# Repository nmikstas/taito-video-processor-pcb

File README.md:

# taito-video-processor-pcb
Reproduction of the Taito video processor PCB. The PCB is designed with Kicad. This project is now complete and verified working!

# Folder Structure
* BOM - Bill of materials
* Gerbers -Gerber files
* pcb - Kicad design files

# PCB Specifications
* Layers: 2
* Dimensions: 305mm X 280mm
* Different PCB Design: 1
* PCB Thickness: 1.6mm
* Surface Finish: HASL
* Castellated Holes: No
* Copper Weight: 1oz.

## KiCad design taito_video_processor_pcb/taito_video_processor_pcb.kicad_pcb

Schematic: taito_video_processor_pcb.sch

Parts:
BT1: 3.6V; battery
BT2: Battery_Cell; CR2032
C1, C2, C3, C4, C5, C6, C7, C8, C10, C11, C12, C13, C15, C16, C17, C18, C19, C20, C21, C23, C24, C25, C26, C27, C28, C29, C30, C32, C33, C34, C35, C36, C37, C38, C39, C40, C41, C43, C46, C47, C48, C49, C50, C51, C52, C53, C54, C55, C56, C57, C58, C59, C60, C62, C64, C66, C67, C68, C69, C70, C71, C72, C73, C74, C75, C76, C78, C79, C81, C82, C83, C84, C85, C86, C87, C91, C92, C93, C94, C95, C99, C100, C102, C103, C104, C105, C106, C107, C108, C999: .1uf; GenericComp
C9, C22, C42, C44, C45, C61, C63, C77, C80: 10uf; CapA
C14, C31: 100pf; GenericComp
C65, C96, C97, C98, C110, C111, C112, C113: 470pf; GenericComp
C88, C89, C90, C109: 100uf; CapB
C101: 10uf; GenericComp
D1: FR156; GenericComp
FB1, FB2, FB3, FB4, FB5, FB6, FB7, FB8, FB9, FB10, FB11, FB12, FB13, FB14: Ferrite_Bead; FB
J1, J2: 14pin; con_14pin
J3, J6: 50pin; 50Pin
J19: 2pin; con_2pin
JB2: W1; JMP
LED1, LED2, LED3, LED4, LED5, LED6: LED
Q1, Q2, Q3, Q4, Q5, Q6, Q7: 2N3904; Trans
Q8: 2N3905; Trans
R1, R9, R10, R11, R12, R21, R22, R23, R24, R25, R26, R27, R36, R51, R52, R53, R54, R55, R56, R57, R58: 33; GenericComp
R2: 1.5k; GenericComp
R3, R4, R5, R15, R18, R49: 270; GenericComp
R6, R38, R60, R62, R66, R67, R68, R69: 3.3k; GenericComp
R7: 220; GenericComp
R8: 2.2k; GenericComp
R13, R20, R46: 82; GenericComp
R14, R19, R28, R48: 180; GenericComp
R16, R17, R45, R65: 150; GenericComp
R29, R30, R31, R32, R33, R47: 470; GenericComp
R34: 680; GenericComp
R35, R61: 390; GenericComp
R37, R50, R59: 47k; GenericComp
R39, R40, R41, R42, R43, R44: 330; GenericComp
R63: 1k; GenericComp
R64: 120; GenericComp
RP1: 1K; RP
RP2: 47K; RP
RP3, RP4, RP5: 3.3k; RP
SW1: SW_Push; Switch
SW2: Switch; Pushbutton
TP1, TP3, TP4: TestPoint; TPA
TP2: 10MHz; TPA
TP5, TP6, TP7, TP8: TestPoint; TPB
U1, U2, U69, U75: 245_1; DIP20
U3, U4: 2114; DIP18
U5, U6, U21, U55, U73, U74, U81, U104: 157_1; DIP16
U7, U36, U89: LS74; DIP14
U8, U9, U22, U49, U67, U88: LS32; DIP14
U10, U11, U12, U13, U14, U15, U16, U17, U26, U27, U28, U29, U30, U31, U32, U33, U41, U42, U43, U44, U45, U46, U47, U48, U59, U60, U61, U62, U63, U64, U65, U66: 4116; DIP16
U18: 68A45; DDIP40
U19: 86_2; DIP14
U20: 86_1; DIP14
U23: 161_1; DIP16
U24, U39, U90: LS04; DIP14
U25, U70, U71, U91, U92, U93, U94: 374_1; DIP20
U34, U72: LS374; DIP20
U35, U52, U53, U54: 153_1; DIP16
U37, U101: LS08; DIP14
U38: 74S113; DIP14
U40, U58: 7417; DIP14
U50: 86_3; DIP14
U51: LS86; DIP14
U56: 2148_1; DIP18
U57: 2148_2; DIP18
U68, U83, U84: 244_2; DIP20
U76: 273_1; DIP20
U77, U78, U79, U80: 373; DIP20
U82: 68A09E; DDIP40
U85, U86: 6514_1; DIP18
U87: LS139; DIP16
U95, U96, U105, U106, U107, U108, U109, U110: 299_1; DIP20
U97, U98: 244_1; DIP20
U99: 138_1; DIP16
U100, U103: LS00; DIP14
U102: LS10; DIP14
Y1: Crystal

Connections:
+5V: C1.1, C10.1, C11.1, C12.1, C13.1, C15.1, C17.1, C20.1, C23.1, C26.1, C27.1, C28.1, C29.1, C30.1, C32.1, C35.1, C39.1, C45.1, C50.1, C51.1, C52.1, C56.1, C60.1, C64.1, C66.1, C67.1, C68.1, C69.1, C70.1, C71.1, C75.1, C79.1, C81.1, C82.1, C83.1, C84.1, C85.1, C86.1, C90.1, C91.1, C92.1, C93.1, C94.1, C95.1, C99.1, C100.1, C102.1, C103.1, C104.1, C105.1, C106.1, C107.1, C108.1, C999.1, FB8.2, LED1.2 (A), LED2.2 (A), LED3.2 (A), LED4.2 (A), LED5.2 (A), LED6.2 (A), Q1.3 (C), Q8.1 (E), R3.1, R4.1, R5.1, R6.1, R28.2, R38.1, R50.1, R59.2, R60.1, R62.1, R63.2, R66.1, R67.1, R68.1, R69.1, RP1.1, RP3.1, RP4.1, RP5.1, U1.20 (VCC), U2.20 (VCC), U3.18 (VSS), U4.18 (VSS), U5.16 (VCC), U6.16 (VCC), U7.14 (VCC), U8.14 (VCC), U9.14 (VCC), U10.9, U11.9, U12.9, U13.9, U14.9, U15.9, U16.9, U17.9, U18.3 (LPSTB), U18.20 (PWR), U19.14 (VCC), U20.14 (VCC), U21.16 (VCC), U22.14 (VCC), U23.16 (VCC), U24.14 (VCC), U25.20 (VCC), U26.9, U27.9, U28.9, U29.9, U30.9, U31.9, U32.9, U33.9, U34.20 (VCC), U35.16 (VCC), U36.14 (VCC), U37.14 (VCC), U38.14 (VCC), U39.14 (VCC), U40.14 (VCC), U41.9, U42.9, U43.9, U44.9, U45.9, U46.9, U47.9, U48.9, U49.14 (VCC), U50.14 (VCC), U51.14 (VCC), U52.16 (VCC), U53.16 (VCC), U54.16 (VCC), U55.16 (VCC), U56.18 (VCC), U57.18 (VCC), U58.14 (VCC), U59.9, U60.9, U61.9, U62.9, U63.9, U64.9, U65.9, U66.9, U67.14 (VCC), U68.20 (VCC), U69.20 (VCC), U70.20 (VCC), U71.20 (VCC), U72.20 (VCC), U73.16 (VCC), U74.16 (VCC), U75.20 (VCC), U76.20 (VCC), U77.20 (VCC), U78.20 (VCC), U79.20 (VCC), U80.20 (VCC), U81.16 (VCC), U82.7 (VCC), U83.20 (VCC), U84.20 (VCC), U87.16 (VCC), U88.14 (VCC), U89.14 (VCC), U90.14 (VCC), U91.20 (VCC), U92.20 (VCC), U93.20 (VCC), U94.20 (VCC), U95.20 (VCC), U96.20 (VCC), U97.20 (VCC), U98.20 (VCC), U99.16 (VCC), U101.14 (VCC), U102.14 (VCC), U103.14 (VCC), U104.16 (VCC), U105.20 (VCC), U106.20 (VCC), U107.20 (VCC), U108.20 (VCC), U109.20 (VCC), U110.20 (VCC)
+12V: C16.1, C18.1, C19.1, C21.1, C22.1, C36.1, C37.1, C41.1, C42.1, C55.1, C59.1, C61.1, C72.1, C76.1, C77.1, C87.1, C89.1, FB10.2, U10.8, U11.8, U12.8, U13.8, U14.8, U15.8, U16.8, U17.8, U26.8, U27.8, U28.8, U29.8, U30.8, U31.8, U32.8, U33.8, U41.8, U42.8, U43.8, U44.8, U45.8, U46.8, U47.8, U48.8, U59.8, U60.8, U61.8, U62.8, U63.8, U64.8, U65.8, U66.8
-5V: C2.1, C3.1, C4.1, C5.1, C6.1, C7.1, C8.1, C9.2, C33.1, C34.1, C38.1, C40.1, C43.1, C44.2, C53.1, C54.1, C57.1, C58.1, C62.1, C63.2, C73.1, C74.1, C78.1, C80.2, C88.2, FB9.2, U10.1, U11.1, U12.1, U13.1, U14.1, U15.1, U16.1, U17.1, U26.1, U27.1, U28.1, U29.1, U30.1, U31.1, U32.1, U33.1, U41.1, U42.1, U43.1, U44.1, U45.1, U46.1, U47.1, U48.1, U59.1, U60.1, U61.1, U62.1, U63.1, U64.1, U65.1, U66.1
AEN: U70.1 (~OE), U71.1 (~OE), U88.6, U90.9, U101.13
BD0: R58.1, U17.2, U33.2, U48.2, U66.2
BD1: R57.1, U16.2, U32.2, U47.2, U65.2
BD2: R56.1, U15.2, U31.2, U46.2, U64.2
BD3: R55.1, U14.2, U30.2, U45.2, U63.2
BD4: R54.1, U13.2, U29.2, U44.2, U62.2
BD5: R53.1, U12.2, U28.2, U43.2, U61.2
BD6: R52.1, U11.2, U27.2, U42.2, U60.2
BD7: R51.1, U10.2, U26.2, U41.2, U59.2
BPWR: C101.1, Q8.3 (C), R61.1, R64.2, U85.18 (VCC), U86.18 (VCC), U100.14 (VCC)
CCLK: U18.21 (CCLK), U23.11 (Q3), U39.3, U102.3
CR0: U74.6, U104.12
CR1: U74.3, U104.9
CR2: U73.13, U104.7
CR3: U73.10, U104.4
CR4: U73.6, U81.12
CR5: U73.3, U81.9
CR6: U55.13, U81.7
CR7: U55.10, U81.4
CR8: U55.6, U72.19 (O7)
CR9: U55.3, U72.16 (O6)
D0: RP2.5, U69.11, U82.31 (D0)
D2: RP2.6, U69.13, U82.29 (D2)
D3: RP2.7, U69.14, U82.28 (D3)
D5: RP2.8, U69.16, U82.26 (D5)
D6: RP2.9, U69.17, U82.25 (D6)
D7: RP2.10, U69.18, U82.24 (D7)
DA0: J6.35, U8.1, U21.6, U39.13
DA1: J6.38, U21.3
DA2: J6.50, U6.13
DA3: J6.49, U6.10
DA4: J6.48, U6.6
DA5: J6.47, U6.3
DA6: J6.36, U5.13
DA7: J6.45, U5.10
DA8: J6.37, U5.6
DA9: J6.40, U5.3
DD0: J6.1, U2.11
DD1: J6.4, U2.12
DD2: J6.3, U2.13
DD3: J6.6, U2.14
DD4: J6.5, U2.15
DD5: J6.8, U2.16
DD6: J6.7, U2.17
DD7: J6.9, U2.18
DPMUX: U2.19 (~E), U36.9 (2Q), U37.2, U37.5
DRW: J6.2, U2.1 (D), U21.13
E: U18.23 (E), U25.6, U37.4, U91.11 (C), U92.11 (C), U93.11 (C), U94.11 (C), U102.9, U103.12
GND: C1.2, C2.2, C3.2, C4.2, C5.2, C6.2, C7.2, C8.2, C9.1, C10.2, C11.2, C12.2, C13.2, C14.2, C15.2, C16.2, C17.2, C18.2, C19.2, C20.2, C21.2, C22.2, C23.2, C24.2, C25.2, C26.2, C27.2, C28.2, C29.2, C30.2, C31.2, C32.2, C33.2, C34.2, C35.2, C36.2, C37.2, C38.2, C39.2, C40.2, C41.2, C42.2, C43.2, C44.1, C45.2, C46.2, C47.2, C48.2, C49.2, C50.2, C51.2, C52.2, C53.2, C54.2, C55.2, C56.2, C57.2, C58.2, C59.2, C60.2, C61.2, C62.2, C63.1, C64.2, C65.2, C66.2, C67.2, C68.2, C69.2, C70.2, C71.2, C72.2, C73.2, C74.2, C75.2, C76.2, C77.2, C78.2, C79.2, C80.1, C81.2, C82.2, C83.2, C84.2, C85.2, C86.2, C87.2, C88.1, C89.2, C90.2, C91.2, C92.2, C93.2, C94.2, C95.2, C96.2, C97.2, C98.2, C99.2, C100.2, C101.2, C102.2, C103.2, C104.2, C105.2, C106.2, C107.2, C108.2, C109.1, C110.2, C111.2, C112.2, C113.2, C999.2, J1.3, J1.5, J1.7, J1.11, J2.4, J3.1, J3.2, J3.4, J6.10, J6.12, J6.24, J6.26, J6.28, J6.29, J6.44, J6.46, J19.1, JB2.2, R2.2, R16.1, R17.1, R37.2, R45.1, RP2.1, SW1.2, SW2.2, U1.10 (GND), U2.10 (GND), U3.9 (GND), U4.9 (GND), U5.8 (GND), U5.15 (~E), U6.8 (GND), U6.15 (~E), U7.2 (1D), U7.7 (GND), U7.12 (2D), U8.7 (GND), U9.7 (GND), U9.12, U9.13, U10.16, U11.16, U12.16, U13.16, U14.16, U15.16, U16.16, U17.16, U18.1 (GND), U19.7 (GND), U20.7 (GND), U21.8 (GND), U21.15 (~E), U22.7 (GND), U23.3, U23.4, U23.5, U23.6, U23.8 (GND), U24.7 (GND), U25.1 (~OE), U25.10 (GND), U26.16, U27.16, U28.16, U29.16, U30.16, U31.16, U32.16, U33.16, U34.10 (GND), U35.1, U35.8 (GND), U35.15, U36.7 (GND), U37.7 (GND), U38.7 (GND), U39.5, U39.7 (GND), U40.7 (GND), U41.16, U42.16, U43.16, U44.16, U45.16, U46.16, U47.16, U48.16, U49.7 (GND), U50.7 (GND), U51.7 (GND), U51.9, U52.1, U52.8 (GND), U52.15, U53.1, U53.8 (GND), U53.15, U54.1, U54.8 (GND), U54.15, U55.8 (GND), U55.15 (~E), U56.8 (~CE), U56.9 (GND), U57.8 (~CE), U57.9 (GND), U58.7 (GND), U59.16, U60.16, U61.16, U62.16, U63.16, U64.16, U65.16, U66.16, U67.7 (GND), U68.1 (~E1), U68.10 (GND), U68.19 (~E2), U69.10 (GND), U70.10 (GND), U71.10 (GND), U72.1 (OE), U72.10 (GND), U73.8 (GND), U73.15 (~E), U74.8 (GND), U74.10, U74.15 (~E), U75.10 (GND), U76.10 (GND), U77.10 (GND), U78.10 (GND), U79.10 (GND), U80.10 (GND), U81.8 (GND), U81.15 (~E), U82.1 (GND), U82.39 (TSC), U83.1 (~E1), U83.10 (GND), U83.19 (~E2), U84.10 (GND), U85.9 (GND), U86.9 (GND), U87.8 (GND), U88.7 (GND), U88.12, U88.13, U89.3 (1CLK), U89.7 (GND), U90.1, U90.3, U90.7 (GND), U90.13, U91.1 (~OE), U91.10 (GND), U92.1 (~OE), U92.10 (GND), U93.1 (~OE), U93.10 (GND), U94.1 (~OE), U94.10 (GND), U95.10 (GND), U96.10 (GND), U97.1 (~E1), U97.10 (GND), U97.19 (~E2), U98.10 (GND), U99.8 (GND), U100.1, U100.2, U100.4, U100.5, U100.7 (GND), U100.9, U100.10, U101.7 (GND), U101.9, U101.10, U102.7 (GND), U103.7 (GND), U104.8 (GND), U104.15 (~E), U105.10 (GND), U106.10 (GND), U107.10 (GND), U108.10 (GND), U109.10 (GND), U110.10 (GND)
HS: U18.39 (HS), U40.1
INV: J6.42, TP1.1, U24.13, U81.1 (S), U103.9, U104.1 (S)
LA0: U71.19, U84.9, U87.14 (2A)
LA1: U71.16, U84.12, U87.13 (2B)
LA2: U54.5, U71.15, U84.7
LA3: U53.11, U71.12, U84.14
LA4: U53.5, U71.9, U84.5
LA5: U35.11, U71.6, U84.16
LA6: U35.5, U71.5, U84.3
LA7: U52.11, U71.2, U84.18
LA8: U52.5, U70.19, U98.18
LA9: U54.6, U70.16, U98.3
LA10: U53.10, U70.15, U98.16
LA11: U53.6, U70.12, U98.5
LA12: U35.10, U70.9, U98.12
LA13: U35.6, U70.6, U98.9
LA14: U52.10, U70.5, U98.7
LA15: U36.5 (1Q), U52.6
LS: U89.11 (2CLK), U102.6, U103.5, U103.10
M0: R25.1, RP1.6, U10.5, U11.5, U12.5, U13.5, U14.5, U15.5, U16.5, U17.5, U26.5, U27.5, U28.5, U29.5, U30.5, U31.5, U32.5, U33.5, U41.5, U42.5, U43.5, U44.5, U45.5, U46.5, U47.5, U48.5, U59.5, U60.5, U61.5, U62.5, U63.5, U64.5, U65.5, U66.5
M1: R27.1, RP1.7, U10.6, U11.6, U12.6, U13.6, U14.6, U15.6, U16.6, U17.6, U26.6, U27.6, U28.6, U29.6, U30.6, U31.6, U32.6, U33.6, U41.6, U42.6, U43.6, U44.6, U45.6, U46.6, U47.6, U48.6, U59.6, U60.6, U61.6, U62.6, U63.6, U64.6, U65.6, U66.6
M2: R26.1, RP1.9, U10.7, U11.7, U12.7, U13.7, U14.7, U15.7, U16.7, U17.7, U26.7, U27.7, U28.7, U29.7, U30.7, U31.7, U32.7, U33.7, U41.7, U42.7, U43.7, U44.7, U45.7, U46.7, U47.7, U48.7, U59.7, U60.7, U61.7, U62.7, U63.7, U64.7, U65.7, U66.7
M3: R11.1, RP1.4, U10.12, U11.12, U12.12, U13.12, U14.12, U15.12, U16.12, U17.12, U26.12, U27.12, U28.12, U29.12, U30.12, U31.12, U32.12, U33.12, U41.12, U42.12, U43.12, U44.12, U45.12, U46.12, U47.12, U48.12, U59.12, U60.12, U61.12, U62.12, U63.12, U64.12, U65.12, U66.12
M4: R24.1, RP1.8, U10.11, U11.11, U12.11, U13.11, U14.11, U15.11, U16.11, U17.11, U26.11, U27.11, U28.11, U29.11, U30.11, U31.11, U32.11, U33.11, U41.11, U42.11, U43.11, U44.11, U45.11, U46.11, U47.11, U48.11, U59.11, U60.11, U61.11, U62.11, U63.11, U64.11, U65.11, U66.11
M5: R23.1, RP1.10, U10.10, U11.10, U12.10, U13.10, U14.10, U15.10, U16.10, U17.10, U26.10, U27.10, U28.10, U29.10, U30.10, U31.10, U32.10, U33.10, U41.10, U42.10, U43.10, U44.10, U45.10, U46.10, U47.10, U48.10, U59.10, U60.10, U61.10, U62.10, U63.10, U64.10, U65.10, U66.10
M6: R22.1, RP1.3, U10.13, U11.13, U12.13, U13.13, U14.13, U15.13, U16.13, U17.13, U26.13, U27.13, U28.13, U29.13, U30.13, U31.13, U32.13, U33.13, U41.13, U42.13, U43.13, U44.13, U45.13, U46.13, U47.13, U48.13, U59.13, U60.13, U61.13, U62.13, U63.13, U64.13, U65.13, U66.13
unnamed: BT1.1 (+), D1.1 (K), R64.1, R65.2
unnamed: BT1.2 (-), BT2.2 (-), JB2.1
unnamed: BT2.1 (+), D1.2 (A)
unnamed: C14.1, R7.1, Y1.2
unnamed: C31.1, R2.1, R8.2, U24.1, Y1.1
unnamed: C65.1, FB7.2, J19.2
unnamed: C109.2, FB11.2
unnamed: FB2.2, R4.2, U40.4
unnamed: FB3.2, R5.2, U40.2, U51.12
unnamed: FB4.2, R15.1
unnamed: FB5.2, R18.1
unnamed: FB6.2, R49.1
unnamed: FB7.1, R66.2, U102.13
unnamed: LED1.1 (K), R39.1
unnamed: LED2.1 (K), R40.1
unnamed: LED3.1 (K), R44.1
unnamed: LED4.1 (K), R43.1
unnamed: LED5.1 (K), R42.1
unnamed: LED6.1 (K), R41.1
unnamed: Q1.1 (E), Q2.3 (C), Q3.3 (C), Q4.3 (C), Q5.3 (C), Q6.3 (C), Q7.3 (C), R29.1, R30.1, R31.1, R32.1, R33.1, R47.1
unnamed: Q1.2 (B), R28.1, R34.2, R35.2
unnamed: Q2.1 (E), R14.1
unnamed: Q2.2 (B), R29.2, U58.2
unnamed: Q3.1 (E), R13.1
unnamed: Q3.2 (B), R30.2, U40.10
unnamed: Q4.1 (E), R19.1
unnamed: Q4.2 (B), R32.2, U40.8
unnamed: Q5.1 (E), R20.1
unnamed: Q5.2 (B), R31.2, U58.12
unnamed: Q6.1 (E), R48.1
unnamed: Q6.2 (B), R33.2, U58.10
unnamed: Q7.1 (E), R46.1
unnamed: Q7.2 (B), R47.2, U58.8
unnamed: Q8.2 (B), R65.1
unnamed: R1.1, U10.3, U11.3, U12.3, U13.3, U14.3, U15.3, U16.3, U17.3
unnamed: R1.2, U49.6
unnamed: R7.2, R8.1, U24.2, U39.1
unnamed: R9.2, U25.19
unnamed: R10.1, U26.3, U27.3, U28.3, U29.3, U30.3, U31.3, U32.3, U33.3
unnamed: R10.2, U49.3
unnamed: R11.2, U35.9
unnamed: R12.2, U37.8
unnamed: R13.2, R14.2, R15.2, R16.2
unnamed: R17.2, R18.2, R19.2, R20.2
unnamed: R21.1, U41.3, U42.3, U43.3, U44.3, U45.3, U46.3, U47.3, U48.3
unnamed: R21.2, U67.3
unnamed: R22.2, U52.7
unnamed: R23.2, U52.9
unnamed: R24.2, U35.7
unnamed: R25.2, U54.7
unnamed: R26.2, U53.7
unnamed: R27.2, U53.9
unnamed: R34.1, U58.6
unnamed: R35.1, U58.4
unnamed: R36.1, U59.3, U60.3, U61.3, U62.3, U63.3, U64.3, U65.3, U66.3
unnamed: R36.2, U67.6
unnamed: R38.2, U51.4
unnamed: R39.2, U72.2 (O0)
unnamed: R40.2, U72.6 (O2)
unnamed: R41.2, U72.12 (O4)
unnamed: R42.2, U72.15 (O5)
unnamed: R43.2, U72.9 (O3)
unnamed: R44.2, U72.5 (O1)
unnamed: R45.2, R46.2, R48.2, R49.2
unnamed: R50.2, U69.15, U82.27 (D4)
unnamed: R59.1, U69.12, U82.30 (D1)
unnamed: R61.2, U40.12, U85.8 (~CS), U86.8 (~CS)
unnamed: TP2.1, U23.2 (C), U25.11 (C), U38.5 (Q), U38.13 (C)
unnamed: TP5.1, U68.4, U82.38 (LIC)
unnamed: TP6.1, U82.33 (BUSY)
unnamed: U1.2, U2.2, U3.11 (D4)
unnamed: U1.3, U2.3, U3.12 (D3)
unnamed: U1.4, U2.4, U3.13 (D2)
unnamed: U1.5, U2.5, U3.14 (D1)
unnamed: U1.6, U2.6, U4.11 (D4)
unnamed: U1.7, U2.7, U4.12 (D3)
unnamed: U1.8, U2.8, U4.13 (D2)
unnamed: U1.9, U2.9, U4.14 (D1)
unnamed: U1.19 (~E), U22.11
unnamed: U3.1 (A6), U4.1 (A6), U5.12
unnamed: U3.2 (A5), U4.2 (A5), U6.4
unnamed: U3.3 (A4), U4.3 (A4), U6.7
unnamed: U3.4 (A3), U4.4 (A3), U6.9
unnamed: U3.7 (A2), U4.7 (A2), U6.12
unnamed: U3.15 (A9), U4.15 (A9), U5.4
unnamed: U3.16 (A8), U4.16 (A8), U5.7
unnamed: U3.17 (A7), U4.17 (A7), U5.9
unnamed: U7.3 (1CLK), U8.11
unnamed: U7.4 (~1PRE_), U8.8
unnamed: U7.10 (~1PRE_), U8.3
unnamed: U7.11 (2CLK), U8.6
unnamed: U8.5, U8.10, U9.6
unnamed: U8.2, U8.13, U9.3
unnamed: U18.4 (MA0), U51.1
unnamed: U18.5 (MA1), U50.12
unnamed: U18.6 (MA2), U50.9
unnamed: U18.7 (MA3), U50.4
unnamed: U18.8 (MA4), U50.1
unnamed: U18.9 (MA5), U19.4, U34.13 (D4)
unnamed: U18.10 (MA6), U20.9, U34.8 (D3)
unnamed: U18.11 (MA7), U20.12, U34.7 (D2)
unnamed: U18.12 (MA8), U20.4, U34.4 (D1)
unnamed: U18.13 (MA9), U20.1, U34.3 (D0)
unnamed: U18.36 (RA2), U19.1, U34.14 (D5)
unnamed: U18.37 (RA1), U19.9, U34.17 (D6)
unnamed: U18.38 (RA0), U19.12, U34.18 (D7)
unnamed: U19.2, U19.5, U19.10, U19.13, U20.2, U20.5, U20.10, U20.13, U51.8
unnamed: U3.6 (A1), U4.6 (A1), U21.4
unnamed: U3.5 (A0), U4.5 (A0), U21.7
unnamed: U3.8 (CS), U4.8 (CS), U21.9, U22.9
unnamed: U21.12, U22.10
unnamed: U21.14, U22.3
unnamed: U3.10 (WE_), U4.10 (WE_), U22.8
unnamed: U23.12 (Q2), U24.11, U25.3
unnamed: U23.13 (Q1), U24.5, U37.13
unnamed: U23.14 (Q0), U24.3, U38.11 (J)
unnamed: U24.6, U25.8
unnamed: U24.10, U25.14
unnamed: U25.9, U37.10, U37.12, U38.12 (K)
unnamed: U9.8, U25.17
unnamed: U25.18, U37.11
unnamed: U36.11 (2CLK), U38.9 (Q)
unnamed: U38.1 (C), U39.2
unnamed: U8.4, U39.10
unnamed: U8.12, U39.12
unnamed: U40.3, U51.11
unnamed: U40.9, U76.12
unnamed: U40.11, U76.9
unnamed: U49.8, U77.1 (~OE)
unnamed: U49.11, U78.1 (~OE)
unnamed: U50.2, U50.5, U50.10, U50.13, U51.2, U51.6, U51.10
unnamed: U55.4, U56.15, U57.15
unnamed: U55.7, U56.16, U57.16
unnamed: U55.9, U56.17, U57.17
unnamed: U55.12, U56.1, U57.1
unnamed: U56.2, U57.2, U73.4
unnamed: U56.3, U57.3, U73.7
unnamed: U56.4, U57.4, U73.9
unnamed: U56.5, U57.5, U74.7
unnamed: U56.6, U57.6, U74.4
unnamed: U56.7, U57.7, U73.12
unnamed: U56.11, U75.2, U76.18
unnamed: U56.12, U75.3, U76.17
unnamed: U56.13, U75.4, U76.14
unnamed: U56.14, U75.5, U76.13
unnamed: U57.11, U75.8, U76.4
unnamed: U57.12, U75.6, U76.8
unnamed: U57.13, U75.7, U76.7
unnamed: U57.14, U75.9, U76.3
unnamed: U58.1, U76.6
unnamed: U58.3, U76.5
unnamed: U58.5, U76.2
unnamed: U58.9, U76.19
unnamed: U58.11, U76.16
unnamed: U58.13, U76.15
unnamed: U67.8, U80.1 (~OE)
unnamed: U67.11, U79.1 (~OE)
unnamed: U68.6, U82.6 (BA)
unnamed: U68.13, U82.32 (R/~W)
unnamed: U68.15, U82.5 (BS)
unnamed: U68.17, U82.36 (AVMA)
unnamed: U69.19 (~E), U90.10
unnamed: U72.11 (Cp), U88.3
unnamed: U76.1 (~R), U89.9 (2Q)
unnamed: U82.8 (A0), U83.11
unnamed: U82.9 (A1), U83.8
unnamed: U82.10 (A2), U83.13
unnamed: U82.11 (A3), U83.6
unnamed: U82.12 (A4), U83.15
unnamed: U82.13 (A5), U83.4
unnamed: U82.14 (A6), U83.17
unnamed: U82.15 (A7), U83.2
unnamed: U82.16 (A8), U97.2
unnamed: U82.17 (A9), U97.17
unnamed: U82.18 (A10), U97.4
unnamed: U82.19 (A11), U97.15
unnamed: U82.20 (A12), U97.8
unnamed: U82.21 (A13), U97.11
unnamed: U82.22 (A14), U97.13
unnamed: U82.23 (A15), U97.6
unnamed: U87.1 (1G), U88.8
unnamed: U85.10 (R/~w), U86.10 (R/~w), U100.11
unnamed: U101.2, U102.12
unnamed: U34.11 (Cp), U101.6
unnamed: U87.15 (2G), U101.11
unnamed: U56.10 (RW), U57.10 (RW), U75.1 (D), U102.8
unnamed: U74.9, U102.10, U102.11
unnamed: U39.8, U103.1
unnamed: U40.13, U103.3
PR6: R6.2, U23.1, U23.7, U23.9, U23.10, U36.1 (~1CLR), U36.4 (~1PRE_), U36.10 (~1PRE_), U36.13 (~1CLR), U38.2 (K), U38.3 (J), U38.4 (S), U38.10 (S)
PR62: R62.2, U89.1 (~1CLR), U89.4 (~1PRE_), U89.10 (~1PRE_), U89.13 (~1CLR)
PR68: R68.2, U95.9, U96.9, U105.9, U106.9, U107.9, U108.9, U109.9, U110.9
PR69: R69.2, U95.2, U95.3, U96.2, U96.3, U105.2, U105.3, U106.2, U106.3, U107.2, U107.3, U108.2, U108.3, U109.2, U109.3, U110.2, U110.3
PU1: RP5.2, U100.12, U101.3
Q: J6.11, U9.9, U25.2, U25.4, U37.1, U102.5
QX: U9.10, U24.9, U25.5, U25.7, U77.11 (C), U78.11 (C), U79.11 (C), U80.11 (C)
R0: U33.14, U78.18, U92.18, U108.7
R1: U32.14, U78.17, U92.17, U107.7
R2: U31.14, U78.14, U92.14, U106.7
R3: U30.14, U78.13, U92.13, U105.7
R4: U29.14, U78.8, U92.8, U96.7
R5: U28.14, U78.7, U92.7, U95.7
R6: U27.14, U78.4, U92.4, U110.7
R7: U26.14, U78.3, U92.3, U109.7
R8: U17.14, U77.18, U91.18, U108.13
R9: U16.14, U77.17, U91.17, U107.13
R10: U15.14, U77.14, U91.14, U106.13
R11: U14.14, U77.13, U91.13, U105.13
R12: U13.14, U77.8, U91.8, U96.13
R13: U12.14, U77.7, U91.7, U95.13
R14: U11.14, U77.4, U91.4, U110.13
R15: U10.14, U77.3, U91.3, U109.13
R16: U66.14, U80.18, U94.18, U108.6
R17: U65.14, U80.17, U94.17, U107.6
R18: U64.14, U80.14, U94.14, U106.6
R19: U63.14, U80.13, U94.13, U105.6
R20: U62.14, U80.8, U94.8, U96.6
R21: U61.14, U80.7, U94.7, U95.6
R22: U60.14, U80.4, U94.4, U110.6
R23: U59.14, U80.3, U94.3, U109.6
R24: U48.14, U79.18, U93.18, U108.14
R25: U47.14, U79.17, U93.17, U107.14
R26: U46.14, U79.14, U93.14, U106.14
R27: U45.14, U79.13, U93.13, U105.14
R28: U44.14, U79.8, U93.8, U96.14
R29: U43.14, U79.7, U93.7, U95.14
R30: U42.14, U79.4, U93.4, U110.14
R31: U41.14, U79.3, U93.3, U109.14
R32: U92.19, U108.5
R33: U92.16, U107.5
R34: U92.15, U106.5
R35: U92.12, U105.5
R36: U92.9, U96.5
R37: U92.6, U95.5
R38: U92.5, U110.5
R39: U92.2, U109.5
R40: U91.19, U108.15
R41: U91.16, U107.15
R42: U91.15, U106.15
R43: U91.12, U105.15
R44: U91.9, U96.15
R45: U91.6, U95.15
R46: U91.5, U110.15
R47: U91.2, U109.15
R48: U94.19, U108.4
R49: U94.16, U107.4
R50: U94.15, U106.4
R51: U94.12, U105.4
R52: U94.9, U96.4
R53: U94.6, U95.4
R54: U94.5, U110.4
R55: U94.2, U109.4
R56: U93.19, U108.16
R57: U93.16, U107.16
R58: U93.15, U106.16
R59: U93.12, U105.16
R60: U93.9, U96.16
R61: U93.6, U95.16
R62: U93.5, U110.16
R63: U93.2, U109.16
S0: U95.1 (S0), U96.1 (S0), U103.6, U105.1 (S0), U106.1 (S0), U107.1 (S0), U108.1 (S0), U109.1 (S0), U110.1 (S0)
S1: U95.19 (S1), U96.19 (S1), U103.8, U105.19 (S1), U106.19 (S1), U107.19 (S1), U108.19 (S1), U109.19 (S1), U110.19 (S1)
SPARE1: C110.1, FB11.1, J1.8
SPARE2: C111.1, FB12.1, J1.12
SPARE3: C112.1, FB13.1, J1.13
VA0: J3.35, RP3.8, U8.9, U18.24 (RS), U21.5, U39.11, U74.5, U83.9, U84.11, U85.5, U86.5, U87.2 (1A)
VA1: J3.23, RP3.9, U21.2, U74.2, U83.12, U84.8, U85.6, U86.6, U87.3 (1B), U88.4
VA2: J3.17, RP3.6, U6.14, U73.14, U83.7, U84.13, U85.7, U86.7
VA3: J3.24, RP3.7, U6.11, U73.11, U83.14, U84.6, U85.4, U86.4
VA4: J3.20, RP3.4, U6.5, U73.5, U83.5, U84.15, U85.3, U86.3
VA5: J3.21, RP3.5, U6.2, U73.2, U83.16, U84.4, U85.2, U86.2
VA6: J3.19, RP3.2, U5.14, U55.14, U83.3, U84.17, U85.1, U86.1
VA7: J3.22, RP3.3, U5.11, U55.11, U83.18, U84.2, U85.17, U86.17
VA8: J3.27, RP4.3, U5.5, U55.5, U85.16, U86.16, U97.18, U98.2, U102.2
VA9: J3.33, RP4.4, U5.2, U55.2, U85.15, U86.15, U97.3, U98.17, U102.1
VA10: J3.28, RP4.5, U97.16, U98.4, U99.1 (A0)
VA11: J3.16, RP4.6, U97.5, U98.15, U99.2 (A1)
VA12: J3.26, RP4.9, U97.12, U98.8, U99.3 (A2)
VA13: J3.18, RP4.10, U97.9, U98.11, U99.4 (E1)
VA14: J3.15, RP4.8, U97.7, U98.13, U99.5 (E2)
VA15: J3.25, RP4.7, TP8.1, U97.14, U98.6, U99.6 (E3), U101.12
VBA: J3.12, U68.14
VBS: J3.7, U68.5
VBSC: J3.48, R67.2, TP7.1, U90.11
VD0: J3.50, R58.2, RP5.3, U1.11, U18.33 (D0), U34.19 (O7), U69.9, U70.18, U71.18, U72.18 (D7), U75.11, U77.19, U78.19, U79.19, U80.19, U86.14
VD1: J3.49, R57.2, RP5.4, U1.12, U18.32 (D1), U34.16 (O6), U69.8, U70.17, U71.17, U72.17 (D6), U75.12, U77.16, U78.16, U79.16, U80.16, U86.13
VD2: J3.47, R56.2, RP5.5, U1.13, U18.31 (D2), U34.15 (O5), U69.7, U70.14, U71.14, U72.14 (D5), U75.13, U77.15, U78.15, U79.15, U80.15, U86.12
VD3: J3.45, R55.2, RP5.6, U1.14, U18.30 (D3), U34.12 (O4), U69.6, U70.13, U71.13, U72.13 (D4), U75.14, U77.12, U78.12, U79.12, U80.12, U86.11
VD4: J3.43, R54.2, RP5.7, U1.15, U18.29 (D4), U34.9 (O3), U69.5, U70.8, U71.8, U72.8 (D3), U75.15, U77.9, U78.9, U79.9, U80.9, U85.14
VD5: J3.41, R53.2, RP5.8, U1.16, U18.28 (D5), U34.6 (O2), U69.4, U70.7, U71.7, U72.7 (D2), U75.16, U77.6, U78.6, U79.6, U80.6, U85.13
VD6: J3.39, R52.2, RP5.9, U1.17, U18.27 (D6), U34.5 (O1), U69.3, U70.4, U71.4, U72.4 (D1), U75.17, U77.5, U78.5, U79.5, U80.5, U85.12
VD7: J3.37, R51.2, RP5.10, U1.18, U18.26 (D7), U34.2 (O0), U36.2 (1D), U69.2, U71.3, U72.3 (D0), U75.18, U77.2, U78.2, U79.2, U80.2, U85.11
VE: J3.13, R63.1, TP4.1, U37.6, U82.34 (E)
VEN: U18.18 (VEN), U89.12 (2D), U101.5
VEQ: J3.36, U25.16, U101.4, U103.2
VLIC: J3.9, U68.16
VMA: J3.10, U68.3
VQ: J3.14, TP3.1, U37.3, U82.35 (Q)
VRW: J3.8, U1.1 (D), U18.22 (R/~W), U22.1, U22.4, U68.7, U69.1 (D), U90.5
VS: U18.40 (VS), U40.5
X0: U51.3, U53.13
X1: U50.11, U53.3
X2: U35.13, U50.8
X3: U35.3, U50.6
X4: U50.3, U52.13
X5: U19.11, U52.3
X6: U19.8, U54.4
X7: U19.3, U53.12
X8: U19.6, U53.4
X9: U20.8, U35.12
X10: U20.11, U35.4
X11: U20.6, U52.12
X12: U20.3, U52.4
_00: U104.13, U108.17
_01: U104.14, U108.8
_02: U104.10, U107.17
_03: U104.11, U107.8
_04: U104.6, U106.17
_05: U104.5, U106.8
_06: U104.3, U105.17
_07: U104.2, U105.8
_10: U81.13, U96.17
_11: U81.14, U96.8
_12: U81.10, U95.17
_13: U81.11, U95.8
_14: U81.6, U110.17
_15: U81.5, U110.8
_16: U81.3, U109.17
_17: U81.2, U109.8
_+5V_: C96.1, FB8.1, J1.1, J1.2
_+12V_: C98.1, FB10.1, J1.6
_-5V_: C97.1, FB9.1, J1.4
_BLUE_: C47.1, FB4.1, J2.10
_CS_: C25.1, FB2.1, J2.2
_GREEN_: C48.1, FB5.1, J2.11
_HS_: C46.1, FB3.1, J2.9
_MRST_: C113.1, FB14.1, J1.14
_RED_: C49.1, FB6.1, J2.14
_VS: FB1.2, J6.30, R3.2, U40.6, U51.13
_VS_: C24.1, FB1.1, J2.1
~5MHZ: U24.4, U76.11 (C), U95.12 (CLK), U96.12 (CLK), U105.12 (CLK), U106.12 (CLK), U107.12 (CLK), U108.12 (CLK), U109.12 (CLK), U110.12 (CLK)
~AEN: U84.1 (~E1), U84.19 (~E2), U90.8, U98.1 (~E1), U98.19 (~E2)
~ASH: U36.3 (1CLK), U70.11 (C), U87.6 (1Y2)
~ASL: U71.11 (C), U87.7 (1Y3)
~CAS: R9.1, RP1.2, U10.15, U11.15, U12.15, U13.15, U14.15, U15.15, U16.15, U17.15, U26.15, U27.15, U28.15, U29.15, U30.15, U31.15, U32.15, U33.15, U41.15, U42.15, U43.15, U44.15, U45.15, U46.15, U47.15, U48.15, U59.15, U60.15, U61.15, U62.15, U63.15, U64.15, U65.15, U66.15
~CCLK: U39.4, U54.3
~DFIRQ: J6.43, U7.6 (~1Q)
~DPMUX: U5.1 (S), U6.1 (S), U21.1 (S), U22.13, U36.8 (~2Q)
~DS0: J6.27, U36.12 (2D)
~DS3: J6.31, U9.1
~E: J6.25, U9.4, U21.11, U25.12, U102.4
~EVEN0: U49.2, U49.13, U87.12 (2Y0)
~EVEN1: U67.5, U67.10, U87.10 (2Y2)
~INV: U24.12, U51.5, U103.4
~MRST: FB14.2, R37.1, U68.2, U82.37 (~RST), U100.13
~MUX: U35.14, U37.9, U38.8 (~Q), U52.14, U53.14, U54.14
~ODD0: U49.5, U49.10, U87.11 (2Y1)
~ODD1: U67.2, U67.13, U87.9 (2Y3)
~Q: U9.2, U21.10, U22.5, U25.15
~QRW: U22.6, U88.2, U88.9
~QX: U24.8, U25.13, U35.2, U52.2, U53.2, U54.2
~RAS: R12.1, RP1.5, U10.4, U11.4, U12.4, U13.4, U14.4, U15.4, U16.4, U17.4, U26.4, U27.4, U28.4, U29.4, U30.4, U31.4, U32.4, U33.4, U41.4, U42.4, U43.4, U44.4, U45.4, U46.4, U47.4, U48.4, U59.4, U60.4, U61.4, U62.4, U63.4, U64.4, U65.4, U66.4
~VEW: U49.1, U49.4, U67.1, U67.4, U103.11
~VFIRQ: J3.3, U7.8 (~2Q), U82.4 (~FIRQ)
~VHALT: J3.11, R60.2, U82.40 (~HALT)
~VIRQ: J3.6, RP3.10, SW1.1, SW2.4, U82.3 (~IRQ)
~VNMI: J3.5, RP4.2, U82.2 (~NMI)
~VRST: U7.1 (~1CLR), U7.13 (~1CLR), U18.2 (~RST), U68.18
~VRW: U49.9, U49.12, U67.9, U67.12, U74.11, U90.6, U101.1, U103.13
~VS0: U22.2, U22.12, U99.15
~VS1: U39.9, U99.14
~VS2: U88.1, U99.13
~VS3: U9.5, U99.12
~VS4: U55.1 (S), U73.1 (S), U74.1 (S), U75.19 (~E), U99.11
~VS5: U88.5, U88.10, U99.10
~VS6: U34.1 (OE), U99.9
~VS7: U18.25 (~CS), U99.7

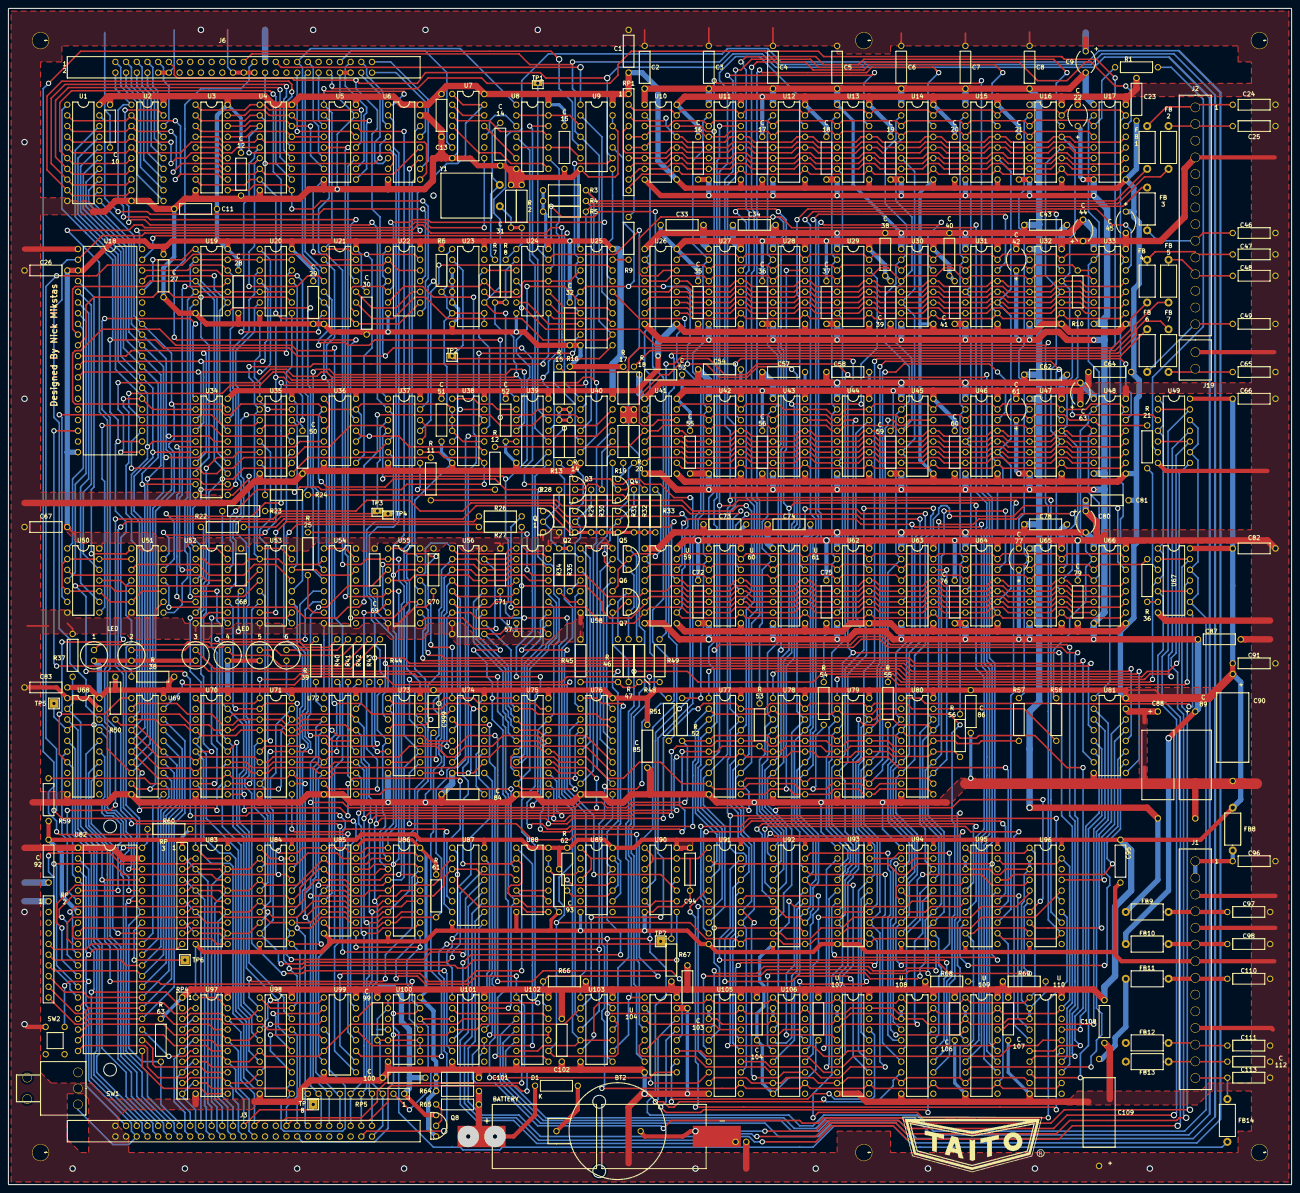
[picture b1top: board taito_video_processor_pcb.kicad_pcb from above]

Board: 2 copper layers, 304.8 x 279.4 mm, 346 parts (0 on the bottom side), 455 nets.

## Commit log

2020-12-11 Began schematic layout
2020-12-12 Continued the schematic layout.
2020-12-13 Continued with the schematic layout.
2020-12-13 Fixed several schematic errors
2021-01-16 Completed schematic capture - still need to fix ERC errors
2021-01-20 Began PCB layout and added all ICs
2021-01-27 Continued layout
2021-07-05 Placed components
2021-07-07 Finished placing components
2021-07-07 Added ground vias
2021-07-10 Began laying down traces to figure out the best spacing and via sizes
2021-07-27 Added traces
2021-07-28 Added more traces
2021-08-01 1285 signal left to connect
2021-09-19 938 disconnected signals remain
2021-09-19 792 disconnected signals remain
2021-09-20 694 disconnected signals remain
2021-09-21 578 disconnected signals remain
2021-09-22 540 disconnected signals remain
2021-09-22 490 disconnected signals remain
2021-09-23 467 disconnected signals remain
2021-09-24 409 disconnected signals remain
2021-09-25 392 disconnected signals remain
2021-09-26 300 disconnected signals remain
2021-09-27 198 disconnected signal remain
2021-09-27 97 disconnected signal remain
2021-09-28 PCB layout complete
2021-10-12 Restructured the project folders. Started the BOM
2021-10-13 Worked on the BOM
2021-10-18 Completed the BOM
2021-10-31 Fixed upper left mounting hole and added CR2032 battery to PCB
2021-10-31 Updated BOM
2021-11-08 Added alternative switch
2021-11-10 Updated the readme file
